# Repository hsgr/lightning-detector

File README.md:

# Lightning Detector

This is a lightning detector design, based upon the schematics published in [Techlib.com](http://www.techlib.com/electronics/lightning.html).

## License

Licensed under the [CERN OHLv1.2](LICENSE).

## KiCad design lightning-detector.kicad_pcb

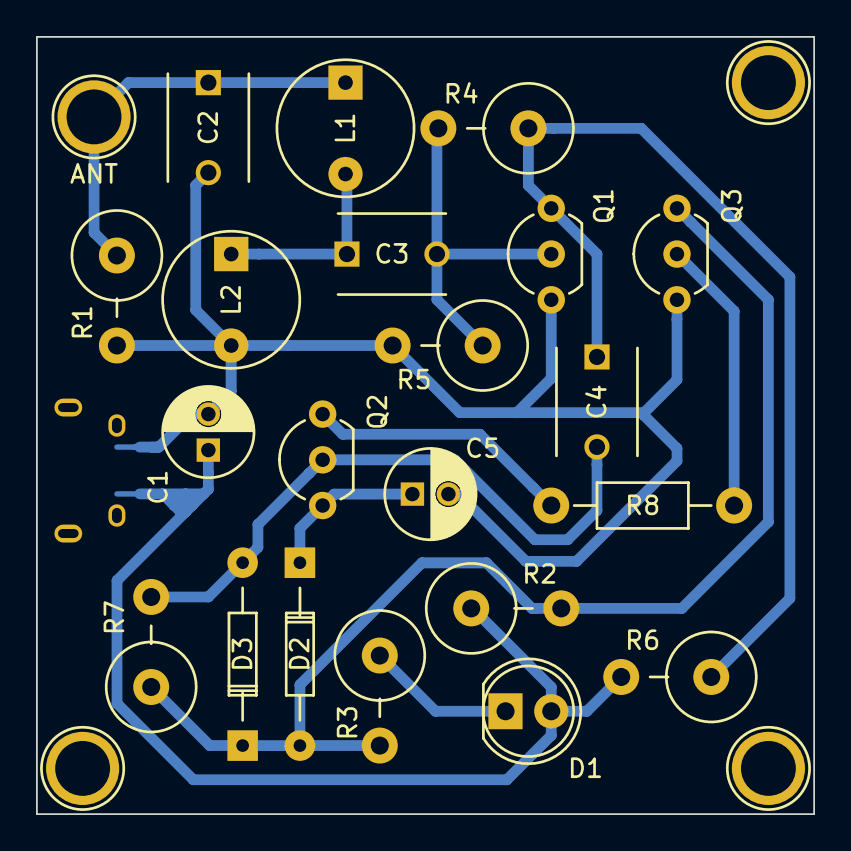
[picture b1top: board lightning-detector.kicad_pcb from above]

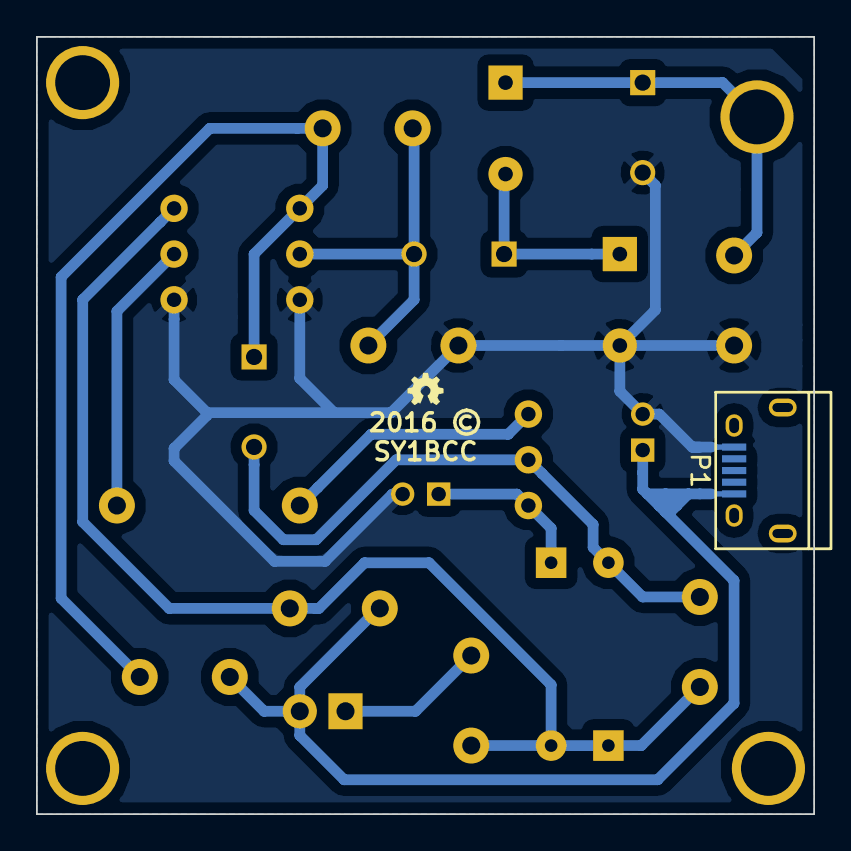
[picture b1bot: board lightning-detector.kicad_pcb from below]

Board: 2 copper layers, 43.2 x 43.2 mm, 24 parts (2 on the bottom side), 12 nets.

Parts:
ANT: CONN_01X01; 1pin
C1: 100u; C_Radial_D5_L11_P2
C2: 10p; C_Disc_D6_P5
C3: 0.001u; C_Disc_D6_P5
C4: 120p; C_Disc_D6_P5
C5: 10u; C_Radial_D5_L11_P2
D1: LED; LED-5MM
D2, D3: 1N914; Diode_DO-35_SOD27_Horizontal_RM10
L1: 10mH; INDUCTOR_V
L2: 1mH; INDUCTOR_V
LOGO_OSHW_silkscreen_2mm: val**; LOGO_OSHW_silkscreen_2mm
P1: USB_OTG; USB_Micro-B
Q1, Q3: 2N4401; TO-92_Inline_Wide
Q2: 2N4403; TO-92_Inline_Wide
R1, R5: 270K; Resistor_Vertical_RM5mm
R2: 1K; Resistor_Vertical_RM5mm
R3: 220; Resistor_Vertical_RM5mm
R4: 1M; Resistor_Vertical_RM5mm
R6: 10K; Resistor_Vertical_RM5mm
R7: 82K; Resistor_Vertical_RM5mm
R8: 3.9K; Resistor_Horizontal_RM10mm

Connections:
GND: C1.2, C2.2, C5.2, L2.2, P1.5, Q1.1, Q3.1, R1.2, R5.2
unnamed: ANT.1, C2.1, L1.1, R1.1
unnamed: C3.1, L1.2, L2.1
unnamed: C3.2, Q1.2, R4.2, R5.1
unnamed: C4.1, Q1.3, R4.1, R6.1
unnamed: C4.2, D2.2, Q2.2, R7.2
unnamed: C5.1, D3.1, Q2.1
unnamed: D1.1, R3.1
unnamed: Q2.3, R8.1
unnamed: Q3.2, R8.2
PLS: D2.1, D3.2, Q3.3, R2.2, R3.2, R7.1
VCC: C1.1, D1.2, P1.1, R2.1, R6.2

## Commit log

2016-01-18 Initial commit.
